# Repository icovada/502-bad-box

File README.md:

# 502 Bad Box

An open source drop-in automation replacement for Bticino Box 502 and bigger
Meant to support up to 8 switches per box and retro-illumination

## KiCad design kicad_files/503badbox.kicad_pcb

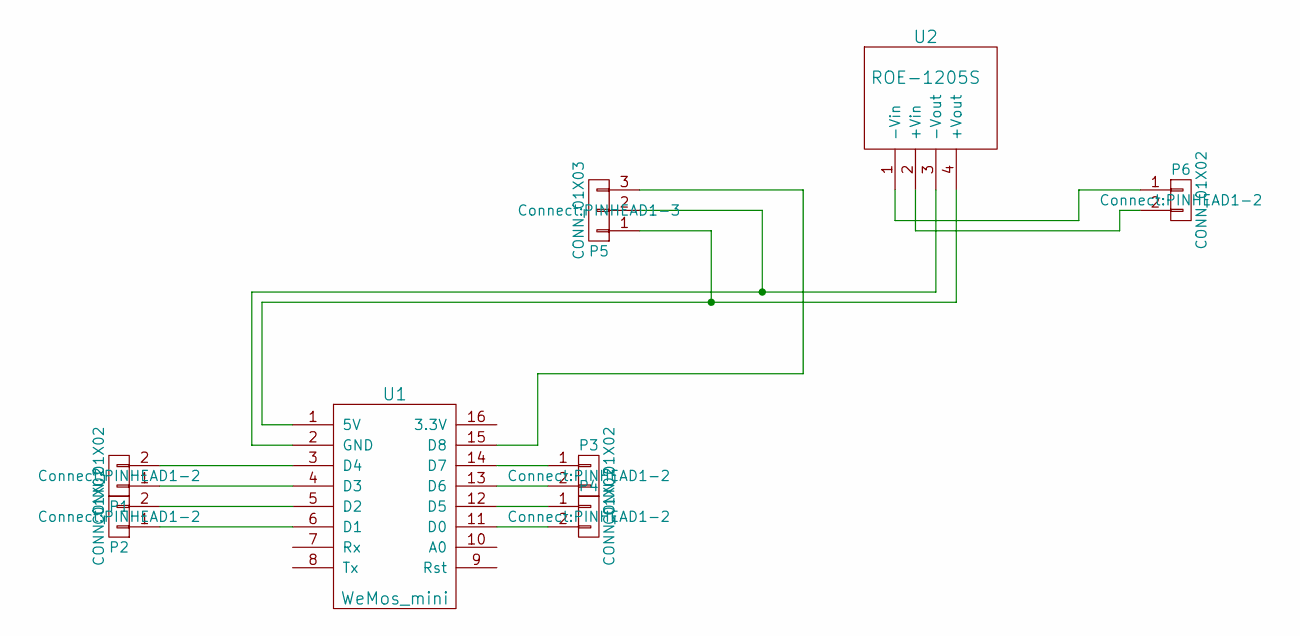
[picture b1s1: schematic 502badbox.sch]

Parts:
P1, P2, P3, P4, P6: CONN_01X02; PINHEAD1-2
P5: CONN_01X03; PINHEAD1-3
U1: WeMos_mini; D1_mini_board
U2: ROE-1205S

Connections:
unnamed: P1.1, U1.4 (D3)
unnamed: P1.2, U1.3 (D4)
unnamed: P2.1, U1.6 (D1)
unnamed: P2.2, U1.5 (D2)
unnamed: P3.1, U1.14 (D7)
unnamed: P3.2, U1.13 (D6)
unnamed: P4.1, U1.12 (D5)
unnamed: P4.2, U1.11 (D0)
unnamed: P5.1, U1.1 (5V), U2.4 (+Vout)
unnamed: P5.2, U1.2 (GND), U2.3 (-Vout)
unnamed: P5.3, U1.15 (D8)
unnamed: P6.1, U2.1 (-Vin)
unnamed: P6.2, U2.2 (+Vin)

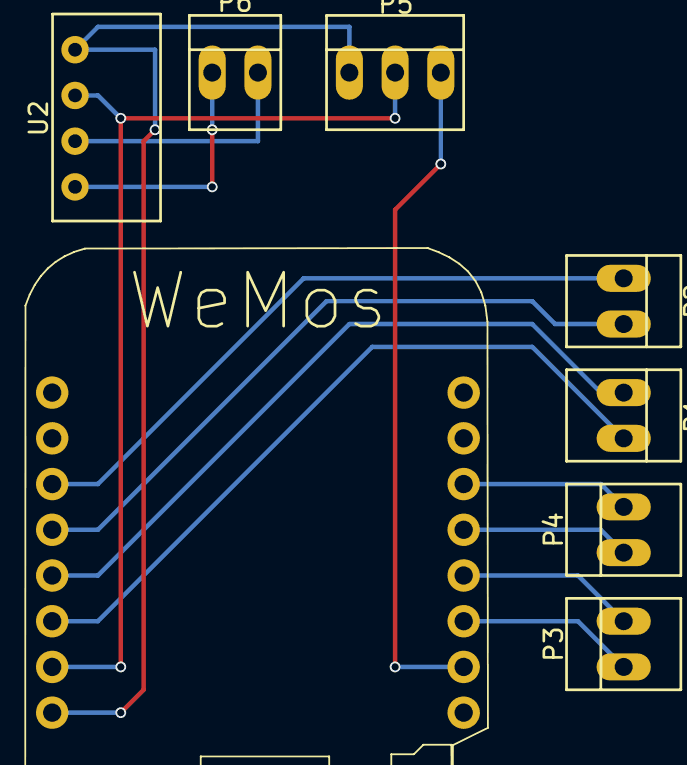
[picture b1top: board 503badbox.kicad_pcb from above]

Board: 2 copper layers, 8 parts (0 on the bottom side), 13 nets.

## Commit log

2018-10-22 Add project files
2018-10-22 Rename 503 to 502
2018-10-24 Initial Arduino code for 503 box. Master will follow
2018-10-24 Implemented debounce Changed from pulldown to internal pullup
2018-10-25 Fix wrong debounce
2018-10-25 First working base slave version
2018-10-25 add sendMessage function to slave
2018-10-25 Master can send messages to slaves
2018-10-25 Basic master/slave functionalities
2018-10-25 Initial working demo
2019-01-04 Add breathing led function
2019-01-04 add gitignore
2019-01-04 Prettify code
2019-01-04 Add LED class
2019-01-04 And now let's run it
2019-01-05 Crashes fter 2 loops
2019-01-05 Add LEDNUMBER variable
2019-01-05 Add strip.Begin() Does not crash anymore
2019-01-05 Working prototype
2019-01-05 Fixed pin reading
2019-01-05 make breathingLed() private to LED
2019-01-05 InputPin can be latching/non-latching and be pressed "single" or "long"
2019-01-05 Comment out config in json
2019-01-06 Added documentation on JSON formatting
2019-01-06 Change MQTT topic to "503-bad-box"
2019-01-06 Adjust message stripping length
2019-01-06 Seems good to me. Time to run it
2019-01-06 Release v0
2019-01-08 Master ID transmitted via JSON
2019-01-08 Do not propagate master info on nodeTimeAdjusted
2019-01-13 Add MQTT node availability report
2019-01-20 Add switch to direct wifi for OTA upgrade
2019-01-22 Working wireless update through web server
2019-01-22 Fix mqtt subscription to match project name
2019-01-23 Update gitignore
